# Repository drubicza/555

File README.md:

# 555
Projects using 555 timer from around the web.

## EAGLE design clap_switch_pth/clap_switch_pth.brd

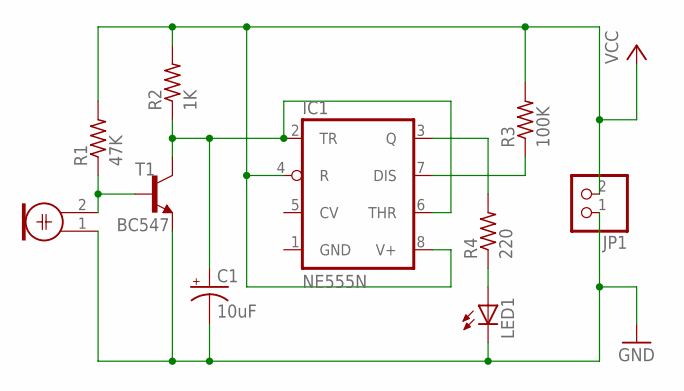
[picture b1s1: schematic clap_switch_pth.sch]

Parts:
C1: 10uF; E2,5-7
IC1: NE555N; DIL08
JP1: PINHD-1X2; 1X02
LED1: LED5MM
M1: MIC; F6050AP
R1: 47K; 0207/7
R2: 1K; 0207/7
R3: 100K; 0207/7
R4: 220; 0207/7
T1: BC547; TO92

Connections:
GND: C1.-, IC1.1 (GND), JP1.1, LED1.K (C), M1.1, T1.1 (E)
unnamed: C1.+, IC1.2 (TR), IC1.6 (THR), R2.1, T1.3 (C)
unnamed: M1.2, R1.1, T1.2 (B)
unnamed: IC1.7 (DIS), R3.1
unnamed: IC1.3 (Q), R4.2
unnamed: LED1.A, R4.1
VCC: IC1.4 (R), IC1.8 (V+), JP1.2, R1.2, R2.2, R3.2

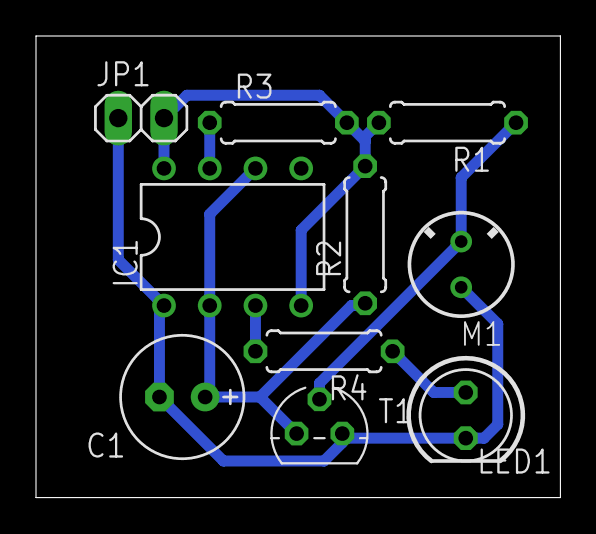
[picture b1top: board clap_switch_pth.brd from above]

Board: 2 copper layers, 29.1 x 25.6 mm, 10 parts (0 on the bottom side), 7 nets.

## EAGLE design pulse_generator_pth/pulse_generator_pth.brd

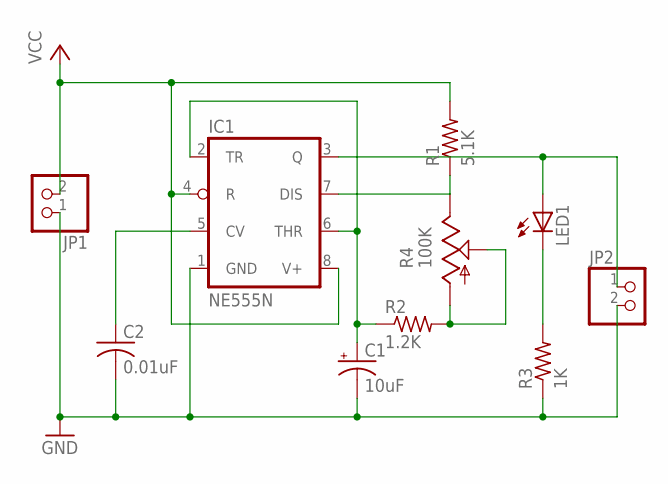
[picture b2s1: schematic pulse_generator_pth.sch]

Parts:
C1: 10uF; E2-5
C2: 0.01uF; C025-040X050
IC1: NE555N; DIL08
JP1, JP2: PINHD-1X2; 1X02
LED1: LED5MM
R1: 5.1K; 0204/7
R2: 1.2K; 0204/7
R3: 1K; 0204/7
R4: 100K; B25U

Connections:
GND: C1.-, C2.2, IC1.1 (GND), JP1.1, JP2.2, R3.1
unnamed: C1.+, IC1.2 (TR), IC1.6 (THR), R2.1
unnamed: R2.2, R4.A, R4.S
unnamed: IC1.7 (DIS), R1.1, R4.E
unnamed: C2.1, IC1.5 (CV)
unnamed: IC1.3 (Q), JP2.1, LED1.A
unnamed: LED1.K (C), R3.2
VCC: IC1.4 (R), IC1.8 (V+), JP1.2, R1.2

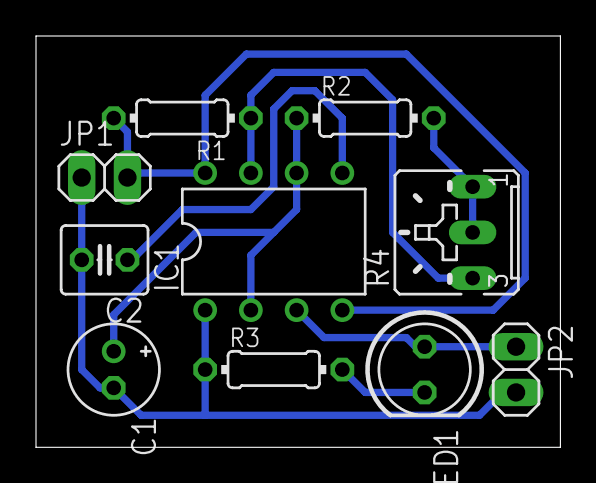
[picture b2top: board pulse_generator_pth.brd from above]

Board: 2 copper layers, 29.1 x 22.8 mm, 10 parts (0 on the bottom side), 8 nets.
